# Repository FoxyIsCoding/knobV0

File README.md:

# SmartKnobV0

 ​

KnobV0 is a simple project that has a microcontroller and a rotary encoder. It can be connected to a pc using Bluethooth or USB. For now it can control the volume and mute/unmute. In future it will be fully configurable thanks to the WiFi support that allows us to make it have a custom WebUI to configure everything in one place.

# Screenshots
Overall :

Schematic:

PCB:

Case:

# BOM:
| Product          | Price      | Link                                                                                                                                                                                                |
|------------------|------------|-----------------------------------------------------------------------------------------------------------------------------------------------------------------------------------------------------|
| Rotary Encoder   | 0,53 EUR   | [AliExpress](https://www.aliexpress.com/item/1005009039521446.html?spm=a2g0o.cart.0.0.704038daCqXtkw&mp=1&pdp_npi=5%40dis%21CZK%21CZK%2015.78%21CZK%2012.79%21%21CZK%2012.79%21%21%21%402103835e17646040474881123ea621%2112000047676722144%21ct%21CZ%216300282529%21%211%210)  |
| The microcontroller | 11,14 EUR  | [RPiShop.cz](https://rpishop.cz/498312/seeed-studio-xiao-esp32s3/)                                                                                                                                  |
| PCB              | 2 EUR      | -                                                                                                                                                                                                   |

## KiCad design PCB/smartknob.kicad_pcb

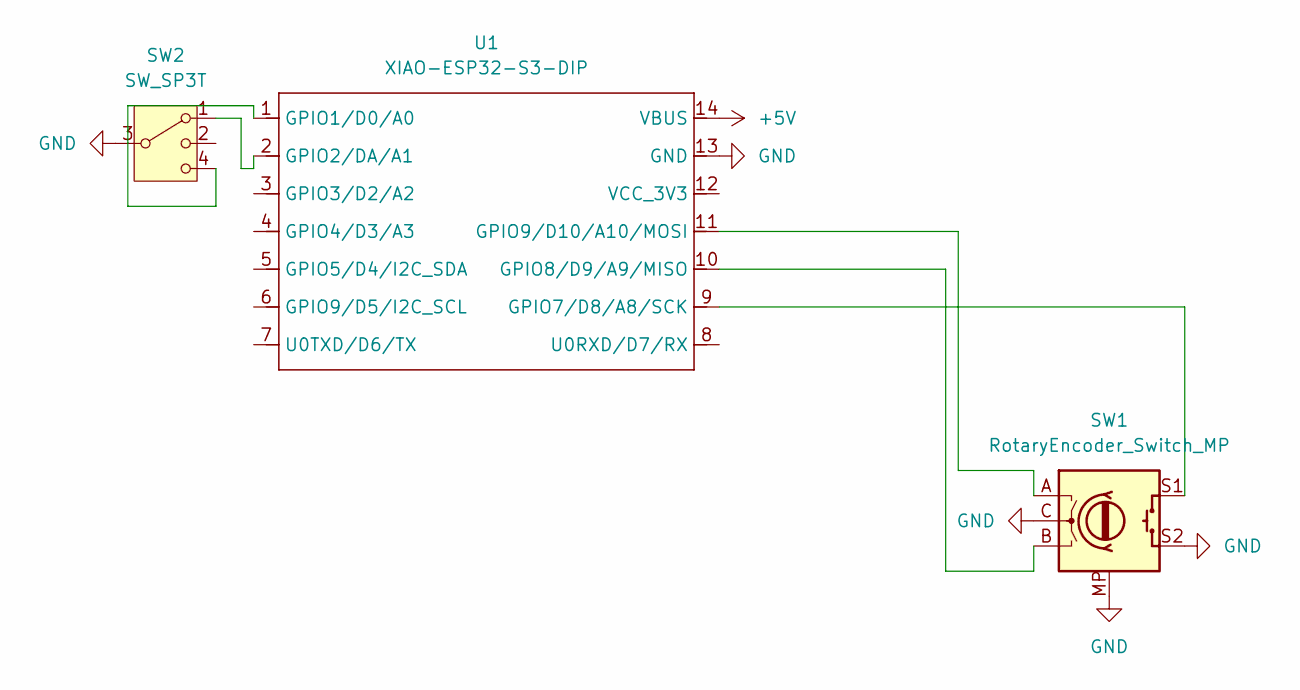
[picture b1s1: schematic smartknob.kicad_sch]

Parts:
SW1: RotaryEncoder_Switch_MP; RotaryEncoder_Alps_EC11E-Switch_Vertical_H20mm
SW2: SW_SP3T; SW_SP3T_PCM13
U1: XIAO-ESP32-S3-DIP; XIAO-ESP32S3-DIP

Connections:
+5V: U1.14 (VBUS)
GND: SW1.C, SW1.MP, SW1.S2, SW2.3, U1.13 (GND)
unnamed: SW2.4, U1.1 (GPIO1/D0/A0)
unnamed: SW2.1, U1.2 (GPIO2/DA/A1)
unnamed: SW1.S1, U1.9 (GPIO7/D8/A8/SCK)
unnamed: SW1.B, U1.10 (GPIO8/D9/A9/MISO)
unnamed: SW1.A, U1.11 (GPIO9/D10/A10/MOSI)

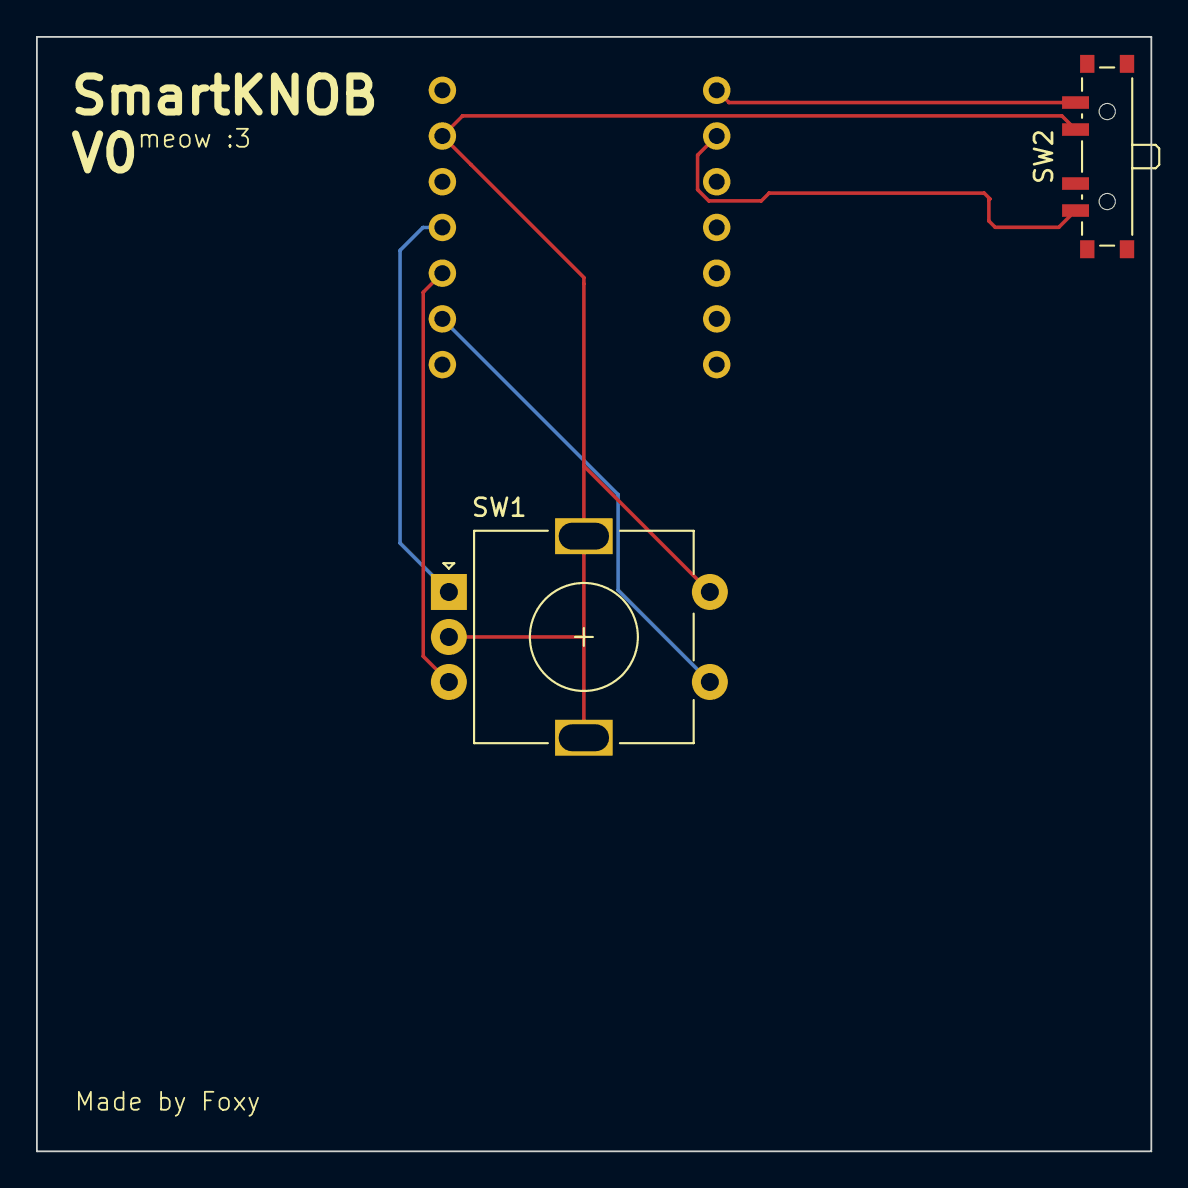
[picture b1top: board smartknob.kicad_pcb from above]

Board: 2 copper layers, 61.9 x 61.9 mm, 3 parts (1 on the bottom side), 6 nets.

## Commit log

2025-11-30 Main Stuff - reused README from older project. not finished yet
2025-11-30 Added basic code, not finished
2025-11-30 Fixed the code and added 3D files
2025-12-01 Fixed PCB design rules
2025-12-02 fixed
2025-12-05 Add BOM table with product prices and links
    Added a BOM table with product details and links.

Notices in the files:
README.md:
License: MIT
